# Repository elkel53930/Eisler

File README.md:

# Eisler 0.1

## Overview

Eisler(アイスラー)は、テキストベースの回路記述言語です。
Eislerで回路を記述し、それを処理系に通すとネットリストと部品表が出力される、
そんなソフトウェアを目指しています。

## Sample

```
defpart R(1:1 2:2){ref "R";}
defpart LED(1:A 2:K){ref "LD";}
defpart NPNTransister(1:E 2:C 3:B){ref "TR";}

defmodule LedWithDriver(1:VPLUS 2:GND 3:IN)
{
  part r_led "330 5% 1608" as R;
  part r_base "1K 5% 1608" as R;
  part led "BR1111C" as LED;
  part tr "2SC1815" as NPNTransister;

  VPLUS - 1.r_led.2 - A.led.K - C.tr.E - GND;
  IN - 1.r_base.2 - B.tr;
}

defpart CONN5(1:1 2:2 3:3 4:4 5:5){ref "CN";}

defmodule main()
{
  part cn "PSS-410153-05" as CONN5;
  module l1,l2,l3 as LedWithDriver;

  wire VIN, GND, LED1, LED2, LED3;

  cn.1 - VIN;
  cn.2 - LED1;
  cn.3 - LED2;
  cn.4 - LED3;
  cn.5 - GND;

  VIN - VPLUS.l1.GND - GND;
  VIN - VPLUS.l2.GND - GND;
  VIN - VPLUS.l3.GND - GND;

  LED1 - IN.l1;
  LED2 - IN.l2;
  LED3 - IN.l3;
}
```

## License

Copyright 2017 elkel53930

Permission is hereby granted, free of charge, to any person obtaining a copy of this software and associated documentation files (the "Software"), to deal in the Software without restriction, including without limitation the rights to use, copy, modify, merge, publish, distribute, sublicense, and/or sell copies of the Software, and to permit persons to whom the Software is furnished to do so, subject to the following conditions:

The above copyright notice and this permission notice shall be included in all copies or substantial portions of the Software.

THE SOFTWARE IS PROVIDED "AS IS", WITHOUT WARRANTY OF ANY KIND, EXPRESS OR IMPLIED, INCLUDING BUT NOT LIMITED TO THE WARRANTIES OF MERCHANTABILITY, FITNESS FOR A PARTICULAR PURPOSE AND NONINFRINGEMENT. IN NO EVENT SHALL THE AUTHORS OR COPYRIGHT HOLDERS BE LIABLE FOR ANY CLAIM, DAMAGES OR OTHER LIABILITY, WHETHER IN AN ACTION OF CONTRACT, TORT OR OTHERWISE, ARISING FROM, OUT OF OR IN CONNECTION WITH THE SOFTWARE OR THE USE OR OTHER DEALINGS IN THE SOFTWARE.

[The MIT License](https://opensource.org/licenses/mit-license.php)

## Author

[elkel53930](https://github.com/elkel53930/)

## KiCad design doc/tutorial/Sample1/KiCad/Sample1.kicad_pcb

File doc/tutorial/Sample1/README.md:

# [.\Sample1.eis] Translation Summary

* Time-stamp : 2017-08-09 15:17:33.6212404 +0900
*  Git revision : master@113192b9846023f26b7f89b9335ecf886028fa2e (Fri Aug 4 16:30:26 2017 +0900)

## BOM

|Ref.|Type|Qty|Search|
|--|--|--:|--|
|CN1|PSS-410153-02|1|[RS](http://jp.rs-online.com/web/c/?sra=oss&r=t&searchTerm=PSS-410153-02), [Google](https://www.google.co.jp/search?q=PSS-410153-02), [Digikey](https://www.digikey.jp/products/ja?keywords=PSS-410153-02), [Chip1Stop](http://www.chip1stop.com/search.do?classCd=&did=&keyword=PSS-410153-02)|
|LD1|BR1111C|1|[RS](http://jp.rs-online.com/web/c/?sra=oss&r=t&searchTerm=BR1111C), [Google](https://www.google.co.jp/search?q=BR1111C), [Digikey](https://www.digikey.jp/products/ja?keywords=BR1111C), [Chip1Stop](http://www.chip1stop.com/search.do?classCd=&did=&keyword=BR1111C)|
|R1|330 5% 1608|1|[RS](http://jp.rs-online.com/web/c/?sra=oss&r=t&searchTerm=330%205%25%201608), [Google](https://www.google.co.jp/search?q=330%205%25%201608), [Digikey](https://www.digikey.jp/products/ja?keywords=330%205%25%201608), [Chip1Stop](http://www.chip1stop.com/search.do?classCd=&did=&keyword=330%205%25%201608)|
## Parts information

|Ref.|Decl.|Type|
|--|--|--|
|CN1|cn@main|PSS-410153-02|
|LD1|led@main|BR1111C|
|R1|r@main|330 5% 1608|
## Nets information

|Net name|Pins|
|--|--|
|$$$00001|led@main . K<br>r@main . 1|
|GND@main|cn@main . GND<br>r@main . 2|
|VIN@main|cn@main . VIN<br>led@main . A|

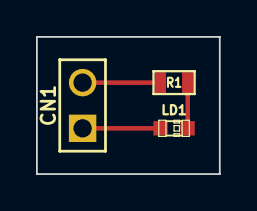
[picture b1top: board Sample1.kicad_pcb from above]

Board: 2 copper layers, 10.2 x 7.6 mm, 3 parts (0 on the bottom side), 3 nets.

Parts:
CN1: CN{Lib=cn-main}; PIN_ARRAY_2X1
LD1: LED{Lib=led-main}; LED-0603
R1: R{Lib=r-main}; SM0603

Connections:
$$$00001: LD1.2, R1.1
GND-main: CN1.2, R1.2
VIN-main: CN1.1, LD1.1

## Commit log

2016-11-10 EislerSpec.mdに追記
2016-11-11 「|」を使った結線の分岐構文を削除
2017-01-12 Parser作成。文法はdata/testcode.eisが正
2017-01-12 parse後の情報にソースコード上のlineとcolumnを追加
2017-01-28 ポートごとにまとめられるようになった。
2017-01-29 リファレンス番号の付与機能を追加。部品一覧の出力機能を追加。
2017-01-29 最低限のデモンストレーションができるようになった。 ・出力されたネットリスト(PADS Logicフォーマット)をNETCHANGERでKiCad形式に変換しアートワークできることまで確認した。
2017-01-30 importに対応。ただし、再帰構造になってると無限ループに陥る
2017-01-31 いくつかの型シノニムをnewtypeに変更 PartIden PortIntLit PortIden ModuleIden CompIden
2017-01-31 Wireを含むConExprと、Wireの宣言のパースができるようになった
2017-02-04 rename combine.hs to Combine.hs
2017-02-14 wireに対応、出力フォーマットをKicad形式に変更
2017-02-14 エクスクラメーションマークで囲むとコメントになるようになった
2017-02-14 ファイルの整理。モジュール名から[Net
2017-02-14 Combine.hsを削除
2017-05-04 行コメント、ブロックコメントを追加。引数なしで起動した場合のメッセージを修正(「PADS用」と表示されるようになっていたところを「KiCad用」に修正)
2017-05-05 サブモジュール実装の前段階として、interface(異なる名前どうしでも接続可能なwire)を実装
2017-05-05 ライセンスをGPLからMITに変更。
2017-05-05 デバッグ出力の削除し忘れを修正
2017-05-05 サブモジュール実装の前段階として、コンポーネント名にモジュール名(今はmain固定)をサフィックスとして追加するようにした。
2017-05-06 サブモジュールに対応
2017-05-06 Semantics.hsのpickupXXXX関数を再帰からfilter&mapの組合せにに書き換え
2017-05-08 BOM出力機能を実装途中
2017-05-08 ネットリストの出力先を標準IOからファイル（入力ファイルの拡張子をnetにしたもの）に変更。BOM出力機能を追加。BOMの出力先は入力ファイルの拡張子をcsvにしたもの。
2017-05-09 サブモジュールの配線が接続されないバグを修正
2017-05-09 part構文で複数のパーツを一括で宣言可能になった。ex. part r1,r2,r3 as R;
2017-05-09 part構文にパーツ名が１つもなくてもエラーにならないバグを修正
2017-05-09 wire構文で複数のワイヤをまとめて宣言に対応
2017-05-09 interface構文で複数のインターフェイスをまとめて宣言に対応
2017-05-09 module構文が複数のmoduleまとめて宣言に対応
2017-05-10 Passive.eisとSemiconductor.eisをBasic.eisに統合
2017-05-10 ファイルを整理
2017-05-17 リネーム時に追加する文字を@から-に変更。PADSネットリストに対応。
2017-05-17 BOMに個数を出力するよう修正。書きかけのチュートリアルを追加
2017-05-19 translate summary出力機能を追加
2017-05-19 SummaryのNets infoにInterfaceを載せないよう変更。不要なファイルを削除
2017-05-19 Summaryのワイヤ名が@ではなく-でつながれていたのを修正
2017-05-20 SummaryにBOM出力を追加
2017-05-20 SummaryがGitHub上で正常に表示されないバグを修正。
2017-05-20 Summaryのタイムスタンプの文字化けを解消
2017-05-20 SummaryのBOM出力でリファレンスを10個ごとに改行する。
2017-05-22 SummaryのBOMの出力順を「部品名でソート」から「リファレンスでソート」に修正
2017-05-24 SummaryにGitのリビジョンを出力する機能を追加。
2017-05-25 ソースコードを整理
2017-06-28 SummaryのBOMで、同じ部品なのに１つの欄にまとめられないことがあるバグを修正。
2017-06-29 コネクタのdefpartを自動生成するツール(eiconn)を追加。
2017-06-29 1pinから200pinまでのコネクタを定義したconn.eisを追加。
2017-07-06 kili423(KiCad4向けフットプリントファイルkicad_modを旧KiCad向けに変換するツール)を追加
2017-07-07 不要なf.closedを削除
2017-07-07 Translation summaryのファイル名をREADME.mdに変更。
2017-07-13 README.mdのタイトル名を修正 README.mdのタイトルが「[README.md] Translation Summary」になっていたので「[入力ファイル名] Translation Summary」に修正。
2017-07-20 importを無視し、同じディレクトリにあるすべてのeisファイルを変換の対象にした。
2017-07-21 Translation SummaryのBOMでSearchにGoogleを追加
2017-07-21 パーサーを修正。 Part,Module,Wire,Itfcについてパースをする部分と、 パースしたものを値コンストラクタでつつむ部分に分けた。 値コンストラクタはローカルとグローバルで分けたいが、 パーサーは共通化したいため。
2017-07-21 パースが通るようになった。
2017-07-21 修正：main以外のmoduleで識別子の重複がエラー処理されていなかった
2017-07-21 モジュールを展開した後に、グローバルコンポーネントをマージするようにした。
2017-07-22 大幅刷新を決意
2017-07-22 アイディアまとめ中
2017-07-24 パーサーの型を書き始めた。
2017-07-24 ポートの省略を廃止して、<>ではなく.でポートを指定することにした。
2017-07-24 defpartステートメントをパースできるようになった。
2017-07-24 Declare partがパースできるようになった。
2017-07-25 パーサを追加
    Declare partのグローバル版とローカル版
    Declare moduleとそのG版L版
    Expression
2017-07-25 ソースコード全体をパースできるようになったが、エラーがおかしい。
    文法にエラーがあるのにエラーが出なかったり、
    エラーの箇所と内容がおかしかったり。
2017-07-25 パーサのエラーメッセージがおかしいのを修正
2017-07-26 パーサが返す型をSourceElementからSrcに変更
2017-07-26 展開後のソースコードの型を作った。
2017-07-26 Types.hs̑啶¬¶~XC³Bæقǂ̂̓RpCʂçȂ¢B
2017-07-26 parseEisler̌^ð¢½B
2017-07-26 一部の型をLens対応にした
2017-07-26 ソースコードを整形
2017-07-26 サブモジュールを展開するコードを書き始めた。
2017-08-01 ピン接続情報を出力する機能を追加
    各部品の各ピンがどのネットに接続されているかの一覧をMarkdownで出力する
    ファイル名はConInfo.mdに固定。
2017-08-04 Expandをコーディング中
2017-08-04 数字で始まる識別子に対応するためのブランチ。
2017-08-04 識別子の先頭文字に数字を使えるようになった。
2017-08-07 チュートリアルを作成中
2017-08-09 構文の説明を作成
2017-08-09 誤字修正
2017-08-09 最初のサンプルのチュートリアルを作成中
2017-08-09 最初のサンプルのチュートリアル作成中。
    EHコネクタはKiCadにデフォルトでフットプリントがないので、
    ヒロスギのピンヘッダに変更した。
2017-08-09 最初のサンプルのチュートリアルを作成
    アートワーク作業についてもう少し詳しく書いた方が良いかも。
2017-08-09 サンプルソースのファイル名を修正
    tu01.eisになっていたので、Sample1.eisに修正
2017-08-09 リファレンスに関する説明をSyntax.mdから削除
    Exposition_of_first_sample.mdに書くことにした。
2017-08-09 最初のサンプルの解説を書いた。
2017-08-09 モジュールについてのチュートリアルを作成中
2017-08-10 モジュールについて書いた。
2017-08-10 モジュールの再帰的宣言に関する注意事項を追記
2017-08-10 ソースコードの分割について説明した。
2017-08-10 Translation Summaryでネット名などの「-」を「@」に変換するのをやめた。
    実際のネット名とサマリに表示される名前が食い違ってしまうため。
2017-08-10 モジュール内のワイヤについて追記
2017-08-10 インターフェイスに関する記述を削除。
2017-08-10 gitignoreðC³
2017-08-10 masterブランチから余計なファイルを削除
2017-08-10 develop_Tutorialブランチから余計なファイルを削除
2017-08-10 インストール手順を修正
2017-08-10 SUMMARYファイルを置いてみた。
2017-08-10 インストールの仕方を追記
2018-04-10 README更新
